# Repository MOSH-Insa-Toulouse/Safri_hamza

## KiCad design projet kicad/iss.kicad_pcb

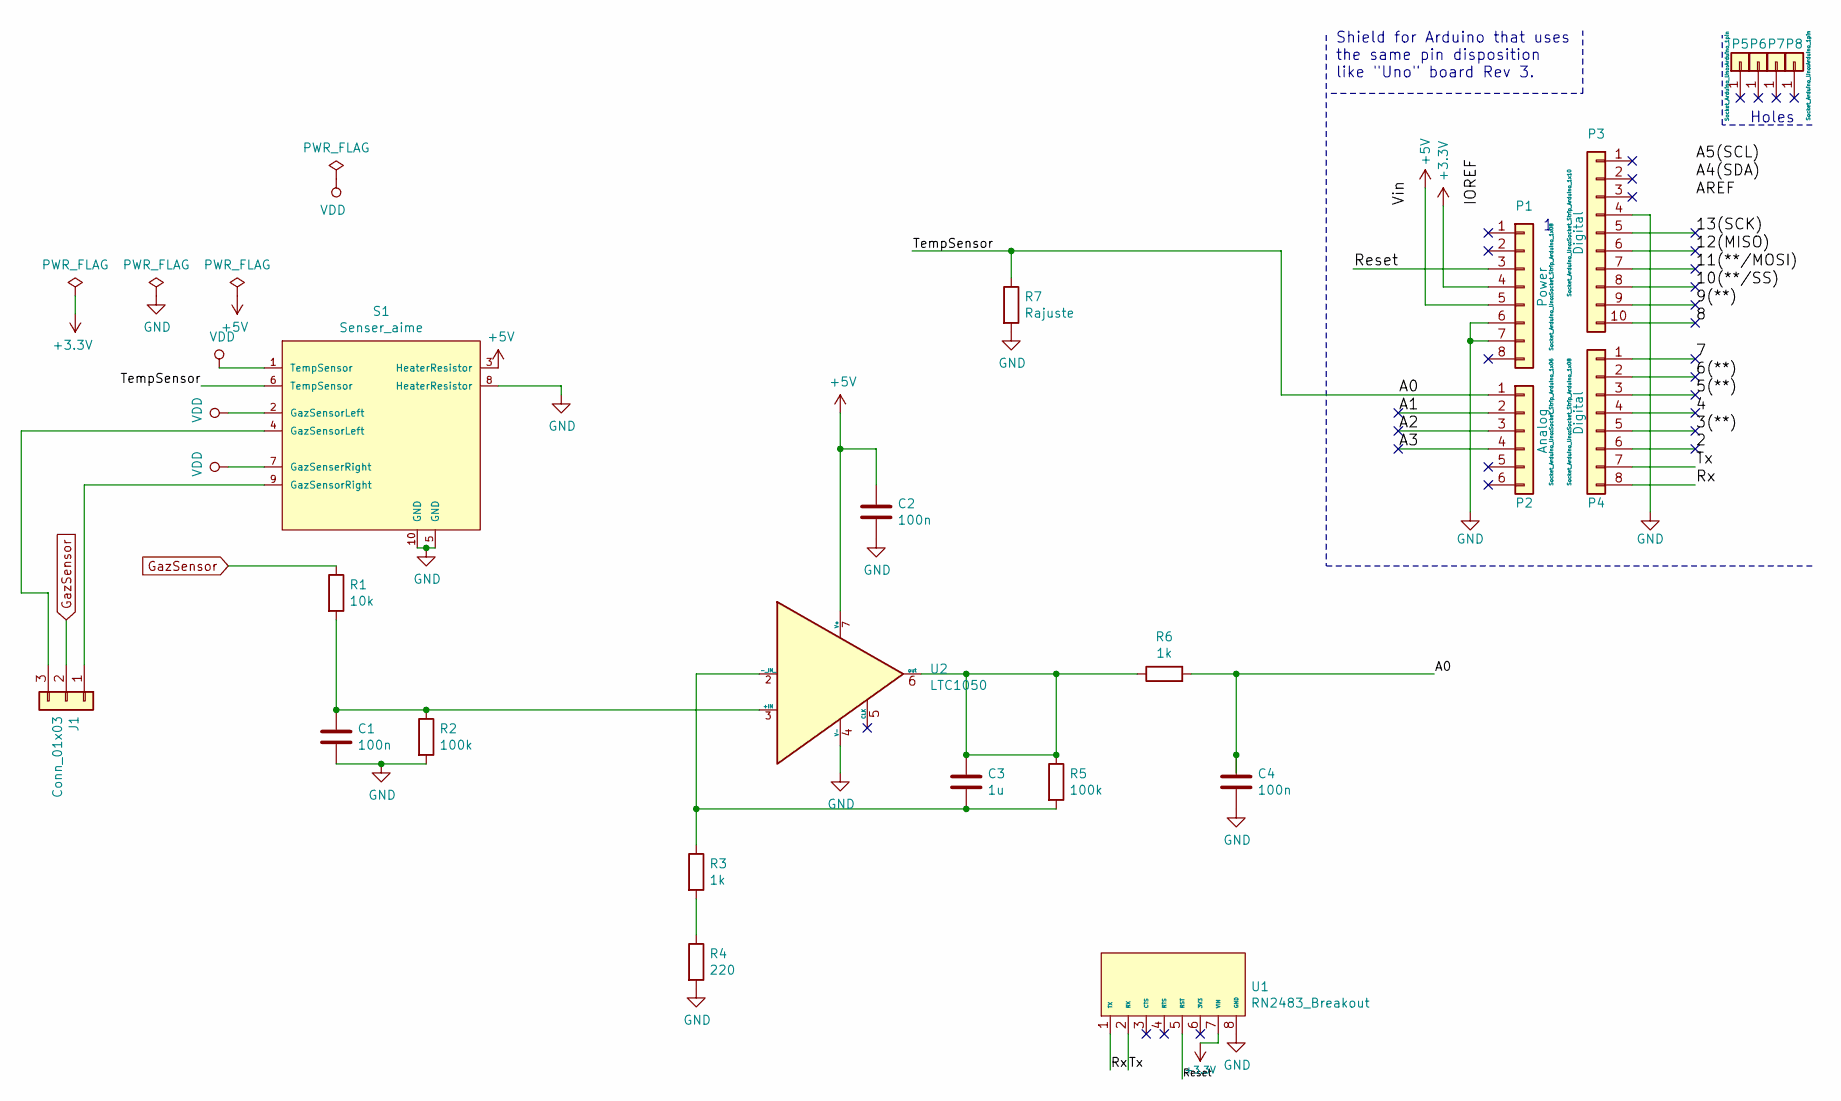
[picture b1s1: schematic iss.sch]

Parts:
C1, C2, C4: 100n; C_Axial_L3.8mm_D2.6mm_P7.50mm_Horizontal
C3: 1u; C_Axial_L3.8mm_D2.6mm_P7.50mm_Horizontal
J1: Conn_01x03; PinHeader_1x03_P2.54mm_Vertical
P1: Power; Socket_Strip_Arduino_1x08
P2: Analog; Socket_Strip_Arduino_1x06
P3: Digital; Socket_Strip_Arduino_1x10
P4: Digital; Socket_Strip_Arduino_1x08
P5, P6, P7, P8: CONN_01X01; Arduino_1pin
R1: 10k; R_Axial_DIN0204_L3.6mm_D1.6mm_P5.08mm_Horizontal
R2, R5: 100k; R_Axial_DIN0204_L3.6mm_D1.6mm_P5.08mm_Horizontal
R3, R6: 1k; R_Axial_DIN0204_L3.6mm_D1.6mm_P5.08mm_Horizontal
R4: 220; R_Axial_DIN0204_L3.6mm_D1.6mm_P5.08mm_Horizontal
R7: Rajuste; R_Axial_DIN0204_L3.6mm_D1.6mm_P5.08mm_Horizontal
S1: Senser_aime; TO-5-10_Window
U1: RN2483_Breakout
U2: LTC1050; DIP-8_W7.62mm_LongPads

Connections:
+3V3: P1.4, U1.7 (VIN)
+5V: C2.1, P1.5, S1.3 (HeaterResistor), U2.7 (V+)
/2: P4.6
/3(**): P4.5
/4: P4.4
/5(**): P4.3
/6(**): P4.2
/7: P4.1
/8: P3.10
/9(**): P3.9
/10(**/SS): P3.8
/11(**/MOSI): P3.7
/12(MISO): P3.6
/13(SCK): P3.5
/A0: C4.1, P2.1, R6.2, R7.1, S1.6 (TempSensor)
/A1: P2.2
/A2: P2.3
/A3: P2.4
/Reset: P1.3, U1.5 (RST)
/Rx: P4.8, U1.1 (TX)
/Tx: P4.7, U1.2 (RX)
GND: C1.2, C2.2, C4.2, P1.6, P1.7, P3.4, R2.2, R4.2, R7.2, S1.5 (GND), S1.8 (HeaterResistor), S1.10 (GND), U1.8 (GND), U2.4 (V-)
GazSensor: J1.2, R1.1
unnamed: C1.1, R1.2, R2.1, U2.3 (+IN)
unnamed: C3.1, R5.1, R6.1, U2.6 (out)
unnamed: C3.2, R3.1, R5.2, U2.2 (-_IN_)
unnamed: J1.1, S1.9 (GazSensorRight)
unnamed: J1.3, S1.4 (GazSensorLeft)
unnamed: R3.2, R4.1
VDD: S1.1 (TempSensor), S1.2 (GazSensorLeft), S1.7 (GazSenserRight)

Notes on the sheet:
Holes
Shield for Arduino that uses the same pin disposition like "Uno" board Rev 3.

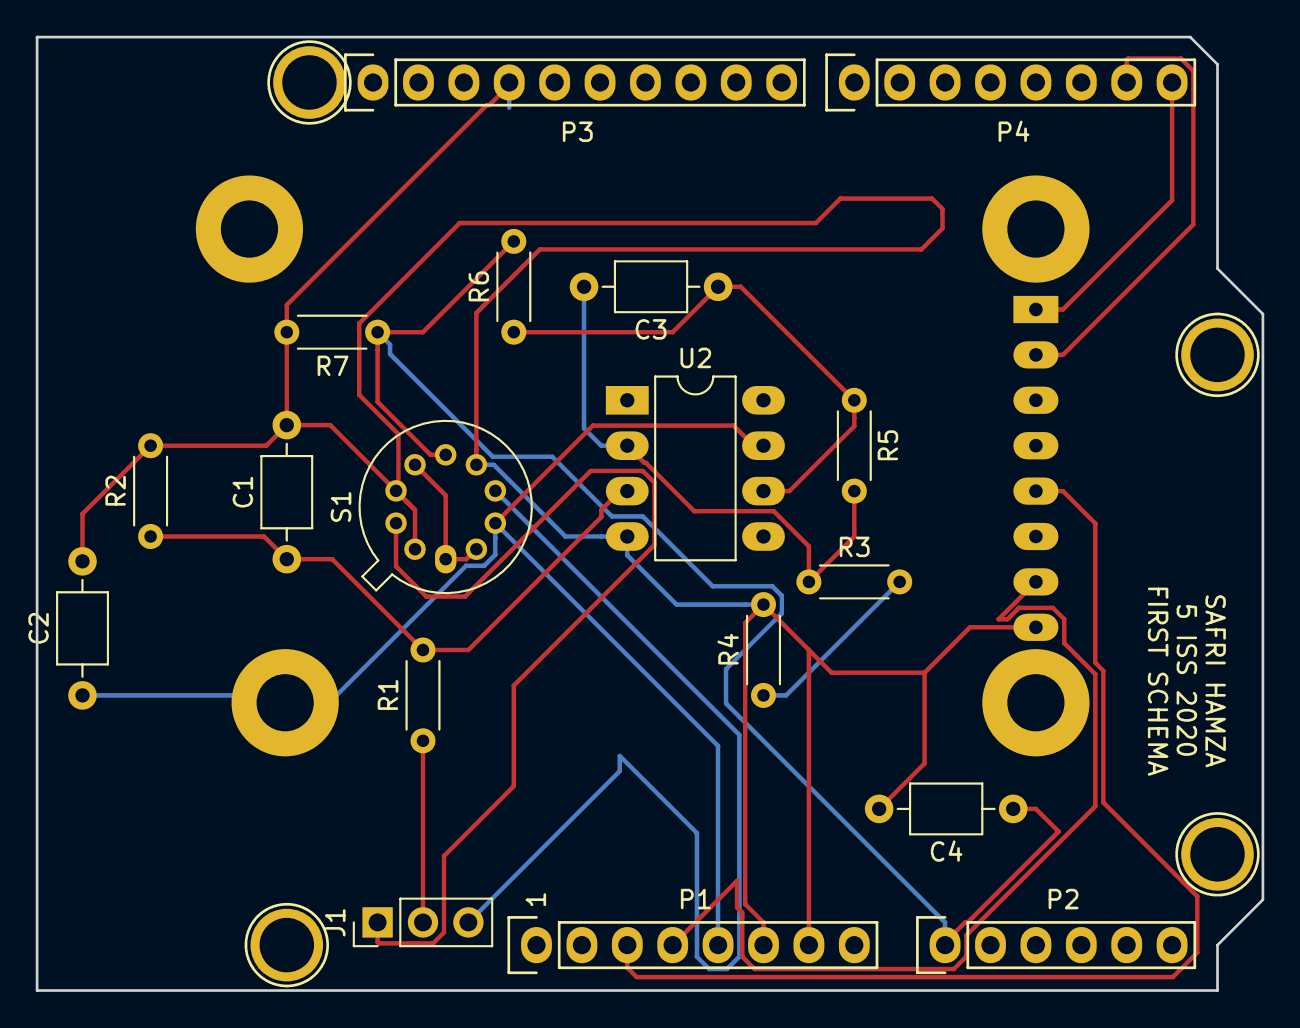
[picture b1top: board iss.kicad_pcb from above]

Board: 2 copper layers, 68.6 x 53.3 mm, 23 parts (1 on the bottom side), 15 nets.

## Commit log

2020-01-22 kicad projet safri hamza
    kicad last version
